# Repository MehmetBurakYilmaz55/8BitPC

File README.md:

> 🇹🇷 [Türkçe versiyon için tıklayın (Turkish Version)](README-tr.md)
# 8-Bit Custom Computer (English)

This project is a permanent, modular PCB hardware revision of the legendary [8-bit breadboard computer architecture by Ben Eater](https://www.youtube.com/playlist?list=PLowKtXNTBypGqImE405J2565dvjafglHU). While the original project was built on breadboards, this repository contains the professional PCB layouts, stabilized power/signal routings, and manufacturing files.

## Modules
### 1. Clock Module (`/Clock-Module`)
The heart of the system.
* **Features:** Adjustable clock frequency, manual single-stepping, and Halt signal support.
* **Design:** Built with NE555 timers and 74LS series logic gates. The routing is optimized for single-layer DIY manufacturing with proper decoupling topology for signal integrity.
> [!NOTE]
> **Project Status / Work in Progress:** The PCB designs for the remaining modules (ALU, Registers, RAM, etc.) have not been completed yet. The bus architecture and PCB connector pinouts are not finalized and are subject to change in future revisions as the system expands.

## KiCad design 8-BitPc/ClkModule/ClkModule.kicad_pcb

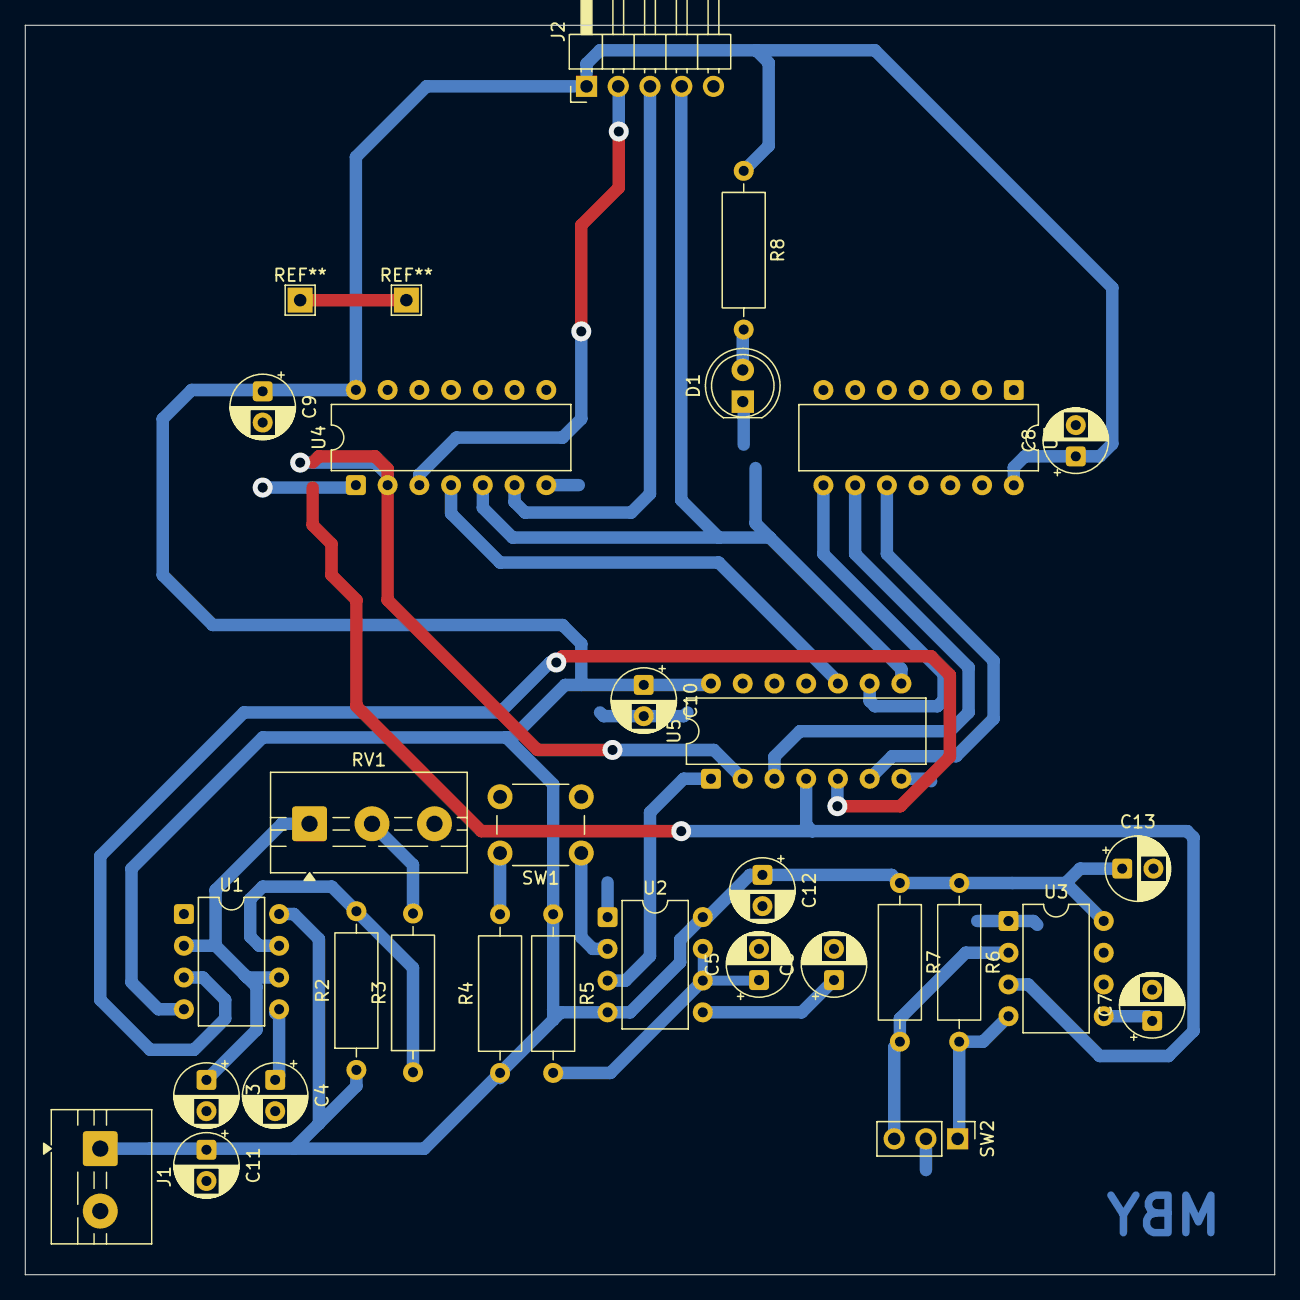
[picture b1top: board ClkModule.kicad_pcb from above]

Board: 2 copper layers, 100.0 x 100.0 mm, 31 parts (1 on the bottom side), 25 nets.

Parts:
C3: 1uF; CP_Radial_D5.0mm_P2.50mm
C4, C6, C7: 0.01uF; CP_Radial_D5.0mm_P2.50mm
C5, C11, C12, C13: 0.1uF; CP_Radial_D5.0mm_P2.50mm
C8, C9, C10: 100nF; CP_Radial_D5.0mm_P2.50mm
D1: LED; LED_D5.0mm
J1: PwrTerminal; TerminalBlock_MaiXu_MX126-5.0-02P_1x02_P5.00mm
J2: ConnPCBus; PinHeader_1x05_P2.54mm_Horizontal
Q1: 2N7002; SOT-23
R2, R3, R4: 1k; R_Axial_DIN0309_L9.0mm_D3.2mm_P12.70mm_Horizontal
R5: 1M; R_Axial_DIN0309_L9.0mm_D3.2mm_P12.70mm_Horizontal
R6, R7: 1K; R_Axial_DIN0309_L9.0mm_D3.2mm_P12.70mm_Horizontal
R8: 330R; R_Axial_DIN0309_L9.0mm_D3.2mm_P12.70mm_Horizontal
RV1: 1M; TerminalBlock_MaiXu_MX126-5.0-03P_1x03_P5.00mm
SW1: SW_Push; SW_PUSH_6mm_H4.3mm
SW2: SW_SPDT; PinHeader_1x03_P2.54mm_Vertical
U1, U2, U3: NE555P; DIP-8_W7.62mm
U4: 74LS04; CERDIP-14_W7.62mm_SideBrazed
U5: 74LS08; CERDIP-14_W7.62mm_SideBrazed
U6: 74LS32; CERDIP-14_W7.62mm_SideBrazed

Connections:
+5V: C8.1, C9.1, C10.1, C11.1, C12.1, C13.1, J1.1, J2.1, R2.1, R4.1, R5.1, R6.1, R7.1, R8.1, U1.4 (~RST), U1.8 (VCC), U2.4 (~RST), U2.8 (VCC), U3.8 (VCC), U4.14 (VCC), U5.14 (VCC), U6.14 (VCC)
/AstableClk: U1.3 (OUT), U5.5
/CLK: J2.4, Q1.1 (G), U4.5, U5.8
/ClkSS: U3.3 (OUT), U4.1, U5.4
/HLT: J2.2, U4.3
/MonostableClk: U2.3 (OUT), U5.1
/~CLK: J2.3, U4.6
GND: C3.2, C4.2, C5.2, C6.2, C7.2, C8.2, C9.2, C10.2, C11.2, C12.2, C13.2, J1.2, J2.5, Q1.2 (S), SW1.2, SW2.2 (B), U1.1 (GND), U2.1 (GND), U3.1 (GND), U3.6 (THRES), U4.7 (GND), U4.9, U4.11, U4.13, U5.7 (GND), U5.12, U5.13, U6.1, U6.2, U6.4, U6.5, U6.7 (GND), U6.12, U6.13
unnamed: D1.2 (A), R8.2
unnamed: D1.1 (K), Q1.3 (D)
unnamed: R3.2, RV1.2
unnamed: R6.2, SW2.1 (A), U3.4 (~RST)
unnamed: R7.2, SW2.3 (C), U3.2 (TRIG)
unnamed: C4.1, U1.5 (CONT)
unnamed: R2.2, R3.1, U1.7 (DISCH)
unnamed: C3.1, RV1.1, U1.2 (TRIG), U1.6 (THRES)
unnamed: C6.1, U2.5 (CONT)
unnamed: C5.1, R5.2, U2.6 (THRES), U2.7 (DISCH)
unnamed: R4.2, SW1.1, U2.2 (TRIG)
unnamed: C7.1, U3.5 (CONT)
unnamed: U4.2, U5.2
unnamed: U4.4, U5.10
unnamed: U5.3, U6.9
unnamed: U5.6, U6.10
unnamed: U5.9, U6.8
